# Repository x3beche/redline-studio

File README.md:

# Workbench

A hardware design workbench. AI agents design the 3D parts, the circuit board and the firmware of one product, together, and check each other's work.

**[redline.medipol.dev](https://redline.medipol.dev)** · in private beta

## The project, in numbers

Straight from Workbench's own analytics for iot-fan.

## 01 · Three rooms, one product

Parts, board and firmware are built against each other. Change the board, and the case and the pin map follow.

- **3D parts.** Three assemblies built from 26 models. Change one part, and everything that uses it is rebuilt.
- **Circuit board.** Real parts from LCSC, placed and routed by TraceMaker: 235 of 235 connections in 121 seconds.
- **Firmware.** Written for the board it runs on. Every pin is named from the schematic, and pins.h is rewritten when the board changes.

## 02 · Draw it, or write it

Mark the model or the board and say what you want. The note keeps the drawing and goes to that room's agent.

- **Draw on the model.** Hold the view, circle what is wrong and say it in a line. The picture and the camera go with the note to the 3D agent.
- **Draw on the board.** The same pen over the layout: circle the part, point where it should go, and say it in your own language.
- **A note becomes a task.** Auto English turns it into English for the agent. Saved as a draft, then queued; the note keeps its drawing and its status.

## 03 · Notes, chat and agents

Ask in Chat. It looks things up with its tools, reads your photos, and writes tasks that go to a room's agent.

### It asks before it guesses.

**On your phone too.** The agents' questions reach Telegram; answer with a button, or send a note with a photo.

## 04 · Analytics

Every call, job and kilowatt-hour since the first note, 21 September to 11 October.

## 05 · Taste

A finished project, distilled into the rules the next one follows. One run read every model, board and firmware in iot-fan.

Every rule was reviewed before it was kept; attach the palette to a project and its agents follow it.

## 06 · Themes

28 themes, 22 dark and 6 light, chosen per browser. The 3D backdrop and the code editor follow.

- **And your own.** Make a theme from any of them and share it as a file; a teammate imports it.
- **Every view follows the theme.** The whole window takes the theme: panels, lines, text and the accent.

## 07 · What it cost

Connect the plans you already pay for. Workbench routes the agents' work through them and prices every call at API rates, so you see what the plans saved.

The plans against API prices: **251.9×**. ₺579,595 of work, paid with ₺2,301 of plans. Three weeks of work, 21 September to 11 October. Claude Max (₺3,170 a month) and Command Code ($5 a month), prorated over 0.67 months.

## 08 · A proxy for part lookups

EasyEDA turns bursts of lookups away. A rotating proxy gives them another way out, with its traffic and cost measured.

- **Its state.** Whether it is on, what went through it this week and what that cost, and whether EasyEDA answers.
- **Always, or when refused.** Every lookup through it, or only the ones EasyEDA turns away. Each lookup comes out somewhere new.
- **Where it came out.** How many addresses and countries, and how often and how fast a lookup worked, with and without it.

## 09 · Why not build it yourself

An agent can write a part. What it needs around it to do a whole product is the rest of this.

| | | |
|---|---|---|
| **Compute** | 1,310 jobs · 35.2 h of CPU · 8.16 kWh | 801 model builds, 342 renders; 78 board runs, 76 layouts, 13 firmware builds; queued, run in containers, timed and metered |
| **Storage** | 677 MB database · 168k documents | 250 built models, 344 MB; 229 source versions, 370 history entries; 195 note pictures, 50 files, 2 releases |
| **Agent API and MCP** | 26 tools over MCP, for any agent | agents connect from their own tools with `REDLINE_TRANSPORT=api` and a token you can revoke; each token sees one workspace; deletes are audited; 221 engineering calculators through `find_tool` and `run_tool` |
| **LLM routing and cost** | 21.8k calls, each priced and counted | 4 providers: Claude API, Command Code, OpenRouter, OpenCode Go; 9 kinds of job, each with its own model; plans you connect, priced against API rates; budgets and spend per note |

## Running it

Workbench is in private beta at [redline.medipol.dev](https://redline.medipol.dev). To run it yourself you need Python 3.12 or newer, Node 20.19 or newer, and a MongoDB connection (Atlas or a local server).

```bash
git clone https://github.com/x3beche/redline-studio.git
cd redline-studio
cp .env.example .env          # fill in MONGODB_URI
./start.sh
```

On first run `start.sh` creates the virtual environment, installs the npm dependencies and starts both servers with live reload: the UI on <http://127.0.0.1:4200>, the API on <http://127.0.0.1:8000>. `./start.sh --build` compiles the UI and serves it from `:8000` alone. `compose.dev.yml` runs the same two servers in containers, with the checkout mounted. To deploy it as a server (`docker compose up -d` or Portainer), see [DEPLOY.md](DEPLOY.md).

The model API keys are not read from `.env`: they are kept in the database and typed in Settings > LLM settings, where each job also picks its provider and model. The board room (atopile, and KiCad with Freerouting in a container), the firmware room (PlatformIO in a container), technical drawings and the Tools tab's checks each need an image built once; without them the rest still works and says what is missing.

To run an agent on your own computer against a Workbench server, use [redline-agent-seed](https://github.com/x3beche/redline-agent-seed) with a token from Agent tokens (the user menu): a start script and a few instructions, which fetch the agents' tools from the server on every start.

- [INSTALL.md](INSTALL.md): requirements, Windows (WSL 2), containers, configuration, the images, Telegram
- [USAGE.md](USAGE.md): the rooms and the everyday loop
- [AGENTS.md](AGENTS.md): for agents working in this repository
- [TOOLS.md](TOOLS.md) · [SECURITY.md](SECURITY.md) · [docs/ACCOUNTS.md](docs/ACCOUNTS.md)

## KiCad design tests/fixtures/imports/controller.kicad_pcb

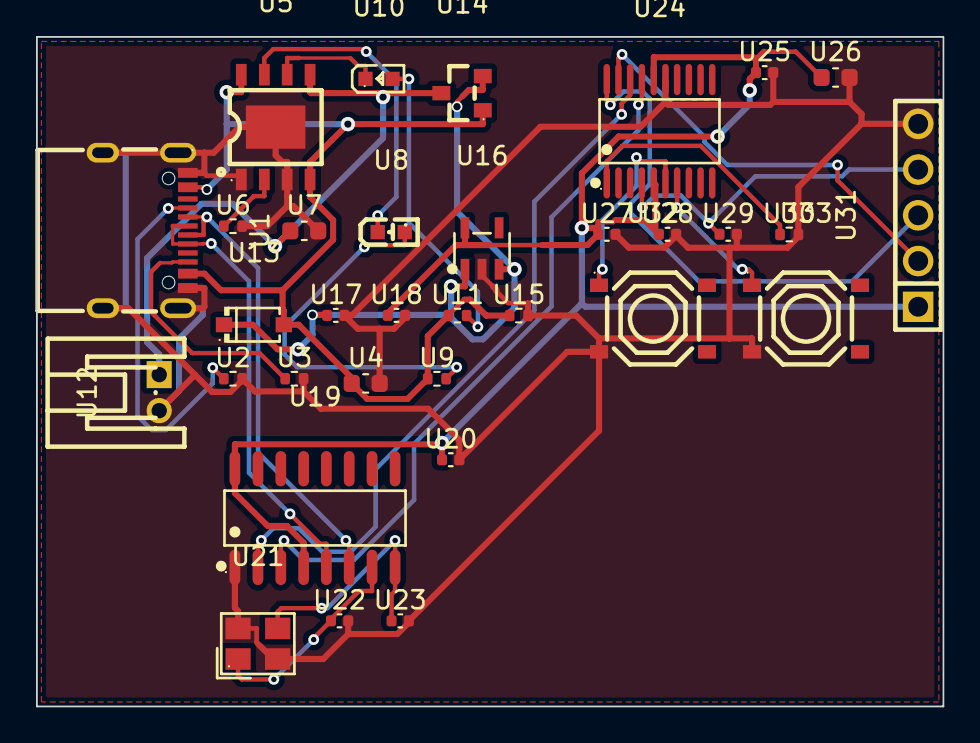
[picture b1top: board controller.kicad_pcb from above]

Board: 2 copper layers, 50.4 x 37.2 mm, 33 parts (0 on the bottom side), 24 nets.

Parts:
U1: ?; C5379909
U2, U3, U6, U9, U11, U15, U30: ?; R_0402_1005Metric
U4, U7, U26: ?; C_0603_1608Metric
U5: ?; C725790
U8: ?; C2286
U10: ?; C12624
U12: ?; C173752
U13: ?; C2685454
U14: ?; C15127
U16: ?; C82942
U17, U18, U20, U22, U23, U25, U27, U28, U29: ?; C_0402_1005Metric
U19: ?; C14267
U21: ?; C49158090
U24: ?; C2969989
U31: ?; C492404
U32, U33: ?; C318884

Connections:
cc1: U1.A5, U2.1
cc2: U1.B5, U3.1
chrg_n: U5.7, U8.2
dn: U1.A7, U1.B7, U19.6
dp: U1.A6, U1.B6, U19.5
gnd: U1.1, U1.2, U1.3, U1.4, U1.A1B12, U1.B1A12, U2.2, U3.2, U4.2, U5.1, U5.3, U5.9, U6.2, U7.2, U12.2, U15.2, U16.2, U17.2, U18.2, U19.1, U20.2, U21.2, U21.4, U22.2, U23.2, U24.15, U25.2, U26.2, U27.2, U28.2, U29.2, U30.2, U31.5, U32.3, U33.3
nrst: U24.4, U29.1, U31.4
pa0: U24.6, U32.1
pa1: U24.7, U33.1
pa13: U24.19, U31.2
pa14: U24.20, U31.3
pb8_boot0: U24.1, U30.1
power.led_chrg-a: U8.1, U9.2
power.led_done-a: U10.2, U11.2
prog: U5.2, U6.1
rxd: U19.3, U24.17
stdby_n: U5.6, U10.1
txd: U19.2, U24.18
v3v3: U16.5, U18.1, U19.4, U19.16, U20.1, U24.5, U24.16, U25.1, U26.1, U27.1, U28.1, U31.1
vbat: U5.5, U7.1, U12.1, U14.3
vbus: U1.A4B9, U1.B4A9, U4.1, U5.4, U5.8, U9.1, U11.1, U13.2, U14.1, U15.1
vsys: U13.1, U14.2, U16.1, U16.3, U17.1
xi: U19.7, U21.1, U22.1
xo: U19.8, U21.3, U23.1
